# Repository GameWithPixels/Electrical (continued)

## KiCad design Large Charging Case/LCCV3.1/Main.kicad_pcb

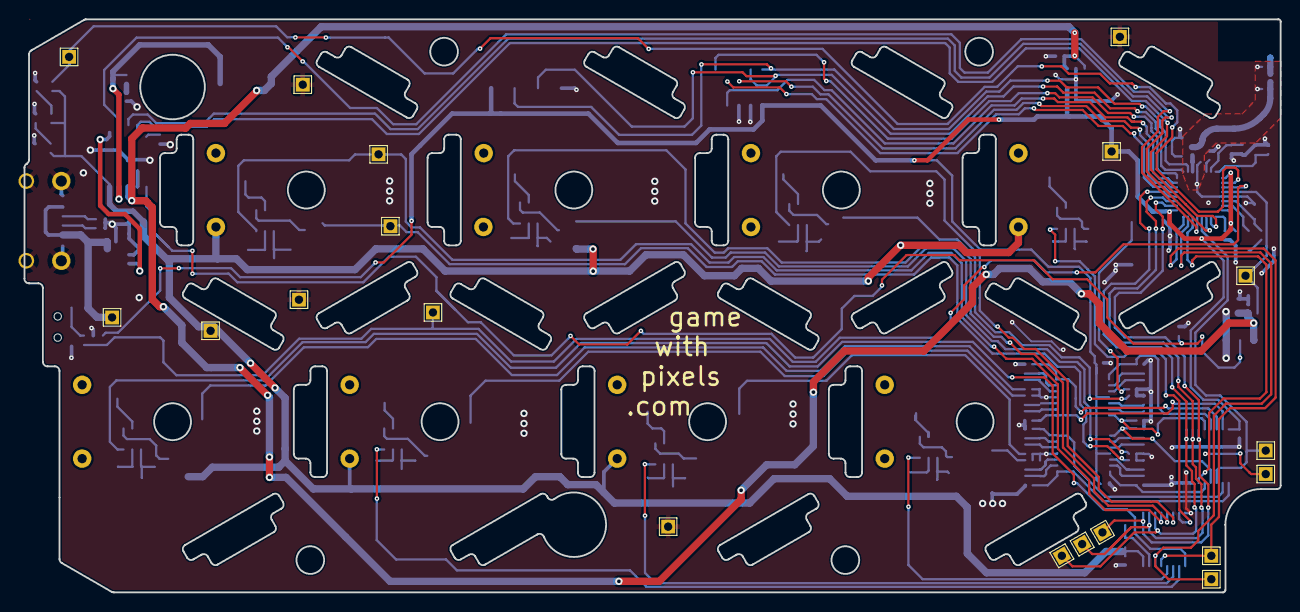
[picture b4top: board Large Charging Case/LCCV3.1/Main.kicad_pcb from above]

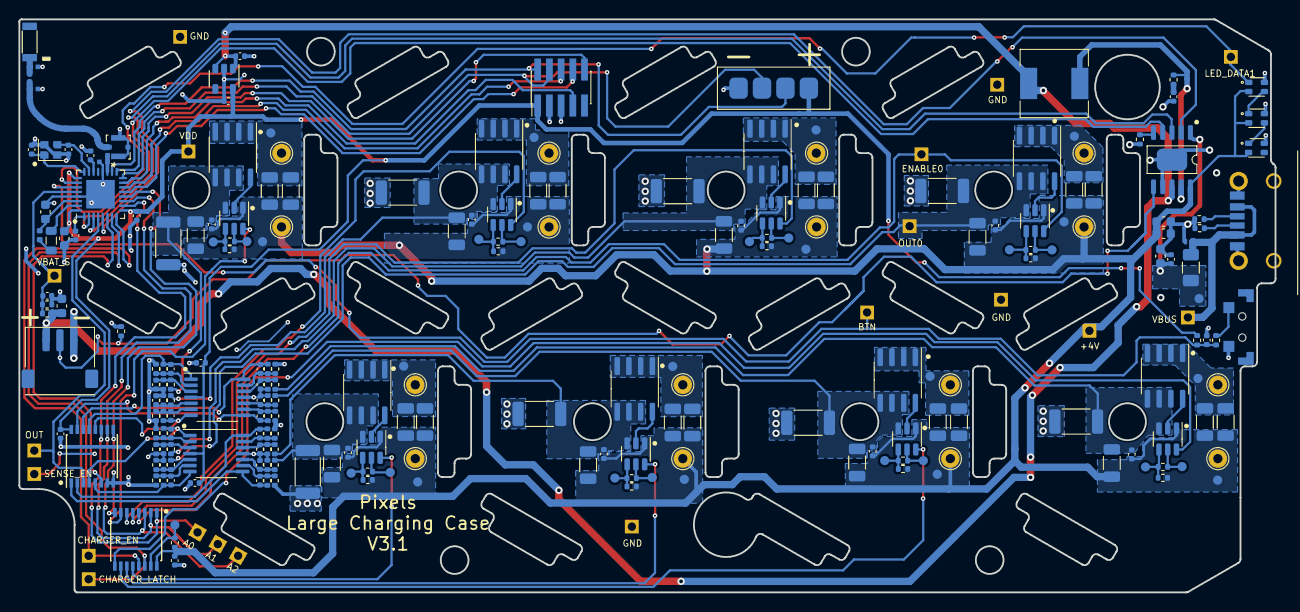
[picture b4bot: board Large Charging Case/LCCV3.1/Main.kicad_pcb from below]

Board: 2 copper layers, 136.2 x 62.1 mm, 256 parts (229 on the bottom side), 117 nets.

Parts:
+4V: +4V; TestPoint_1.5x1.5_Drill0.9mm
A0: A0; TestPoint_1.5x1.5_Drill0.9mm
A1: A1; TestPoint_1.5x1.5_Drill0.9mm
A2: A2; TestPoint_1.5x1.5_Drill0.9mm
AE1: Antenna_Chip; CHIP_ANT
BTN: BTN; TestPoint_1.5x1.5_Drill0.9mm
C1, C2: 4.7uF 6.3V 20%; C_0603_1608Metric
C3, C4, C10, C11, C15, C19, C23, C27, C31, C35, C39, C40, C41, C42, C43, C49, C50, C55, C59, C60, C61, C62, C63, C64, C65, C66, C67, C68, C69, C70, C71, C72: 0.1uF 10V 20%; C_0402_1005Metric
C5, C6: 8pF 10V 10%; C_0402_1005Metric
C7: 100pF NP0 10V 5%; C_0402_1005Metric
C8, C9: 0.8pF 10V 5% NP0; 0402_RF
C12, C16, C20, C24, C28, C32, C36, C56: 47uF 10V 20%; C_1206_3216Metric
C13, C17, C21, C25, C29, C33, C37, C57: 100nF 50V NP0; C_1206_3216Metric
C14, C18, C22, C26, C30, C34, C38, C58: 56nF 50V NP0; C_1206_3216Metric
C44, C45: 10uF 10V 20%; C_0603_1608Metric
C46: 3.3nF 10V 20%; C_0402_1005Metric
C47, C48: 22uF 10V 20%; C_0603_1608Metric
C52, C53: 10uF 10V 20%; C_0402_1005Metric
C54: 10nF 25V 10%; C_0402_1005Metric
C73: DNP; 0402_RF
CHARGER_EN: CHARGER_EN; TestPoint_1.5x1.5_Drill0.9mm
CHARGER_LATCH: CHARGER_LATCH; TestPoint_1.5x1.5_Drill0.9mm
D1, D2, D3: TX1812Z_2020
D5: D_TVS; DFN
ENABLE0: ENABLE0; TestPoint_1.5x1.5_Drill0.9mm
F1: 1500mA <150mR; Fuse_1206_3216Metric
GND: GND; TestPoint_1.5x1.5_Drill0.9mm
GND#2, GND#3, GND#4: GND; TestPoint_1.5x1.5_Drill0.9mm
J1: Conn_02x05_Odd_Even; PinHeader_2x05_P1.27mm_Vertical_SMD
J2, J5, J8, J11, J14, J17, J20, J25: Coil B; TestPoint_THTPad_D2.0mm_Drill1.0mm
J3, J6, J9, J12, J15, J18, J21, J26: TX_Coil; TX Coil
J4, J7, J10, J13, J16, J19, J22, J27: Coil A; TestPoint_THTPad_D2.0mm_Drill1.0mm
J23: USB_C_Receptacle_USB2.0; USB-C-SMD_10P-P1.00-L6.8-W8.9
J24: Conn_01x03; Battery_Socket_1.5mm_3PIN
J28: DNP; MFH3.RECE.20369.001E.01
L1: 10uH 100mA 10%; L_0805_2012Metric
L2: 15nH; L_0402_1005Metric
L3: 1.5nH 5%; 0402_RF
L4: 2.2uH 1.5A 10%; SPM6530
L6: 3.9nH 5%; 0402_RF
LED_DATA1: LED_DATA1; TestPoint_1.5x1.5_Drill0.9mm
OUT: OUT; TestPoint_1.5x1.5_Drill0.9mm
OUT0: OUT0; TestPoint_1.5x1.5_Drill0.9mm
P1: heard4; 4x2.54mm_SMD
R1: 10k 5%; R_0402_1005Metric
R2: 1k 1%; R_0402_1005Metric
R3, R5, R7, R9, R11, R13, R15, R37: 200k 1%; R_0402_1005Metric
R4, R6, R8, R10, R12, R14, R16, R38: 84.5k 1%; R_0402_1005Metric
R17: 82K 1%; R_0402_1005Metric
R18: 120k 1%; R_0402_1005Metric
R20: 100k 1%; R_0402_1005Metric
R21, R25, R28, R32, R39, R43, R44, R48, R49, R53, R54, R58, R59, R63, R64, R68: 100k 0.1%; R_0402_1005Metric
R22, R24, R29, R31, R40, R42, R45, R47, R50, R52, R55, R57, R60, R62, R65, R67: 2k 0.1%; R_0402_1005Metric
R23, R30, R41, R46, R51, R56, R61, R66: 100mR 0.5W 1%; R_2010_5025Metric
R26, R27: 5.1k 1%; R_0402_1005Metric
R34: 4.02M 1%; R_0402_1005Metric
R36: 10M 1%; R_0402_1005Metric
R69: 1R 5%; R_0402_1005Metric
SENSE_EN: SENSE_EN; TestPoint_1.5x1.5_Drill0.9mm
SW1: SW_Push; TSB002
U1: N52810_QFN32; QFN-32-1EP_5x5mm_P0.5mm_EP3.1x3.1mm
U2, U4, U6, U8, U10, U12, U14, U23: XKT001; SOT-23-6
U3, U5, U7, U9, U11, U13, U15, U24: XKT335; SOIC-8_3.9x4.9mm_P1.27mm
U16: ETA9882; ESSOP10
U17: 74HC4051PW; SSOP-16_4.4x5.2mm_P0.65mm
U18, U20: LM2902; TSSOP-14_4.4x5mm_P0.65mm
U19: 74HCT259; SSOP-16_4.4x5.2mm_P0.65mm
U22: ME6215; SOT-23-5
VBAT_S: VBAT_S; TestPoint_1.5x1.5_Drill0.9mm
VBUS: VBUS; TestPoint_1.5x1.5_Drill0.9mm
VDD: VDD; TestPoint_1.5x1.5_Drill0.9mm
W4, W5, W8, W9, W10, W13, W14, W15, W18, W19, W20, W23, W24, W25, W28, W29, W30, W33, W34, W35, W38, W71, W72, W75: R; TEST_PIN
W7, W12, W17, W22, W27, W32, W37, W74: D; TEST_PIN
W59: CHARGER_CLR; TEST_PIN
W62: 5V; TEST_PIN
Y1: 32MHz 40ppm; Crystal_SMD_2016-4Pin_2.0x1.6mm

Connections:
+4V: +4V.1, C11.1, C12.1, C13.2, C14.2, C15.1, C16.1, C17.2, C18.2, C19.1, C20.1, C21.2, C22.2, C23.1, C24.1, C25.2, C26.2, C27.1, C28.1, C29.2, C30.2, C31.1, C32.1, C33.2, C34.2, C35.1, C36.1, C37.2, C38.2, C42.1, C47.1, C48.1, C55.1, C56.1, C57.2, C58.2, D1.2 (VCC), D2.2 (VCC), D3.2 (VCC), J2.1, J5.1, J8.1, J11.1, J14.1, J17.1, J20.1, J25.1, R3.2, R5.2, R7.2, R9.2, R11.2, R13.2, R15.2, R20.1, R37.2, U2.1 (VDD), U4.1 (VDD), U6.1 (VDD), U8.1 (VDD), U10.1 (VDD), U12.1 (VDD), U14.1 (VDD), U16.10 (VOUT), U19.16 (VCC), U23.1 (VDD), W4.1, W9.1, W14.1, W19.1, W24.1, W29.1, W34.1, W71.1
+5V: C43.1, C44.1, F1.2, U16.1 (VIN), W62.1
+BATT: C45.1, C53.1, J24.3, L4.2, R34.1, U16.8 (BAT), U22.1 (VIN), U22.3 (CE)
/ANTENNA: AE1.1 (FEED), C73.1, L3.2
/ANT_50: C8.1, J28.4 (RF), L3.1, L6.2
/ANT_NRF: C9.1, L6.1, U1.19 (ANT)
/Multiplexed Chargers/CHARGER_ENL_D: CHARGER_EN.1, U1.8 (P0.10), U19.13 (D)
/Multiplexed Chargers/CHARGER_SELECT_A0: A0.1, U1.10 (P0.12), U17.11 (A), U19.1 (A0)
/Multiplexed Chargers/CHARGER_SELECT_A1: A1.1, U1.11 (P0.14), U17.10 (B), U19.2 (A1)
/Multiplexed Chargers/CHARGER_SELECT_A2: A2.1, U1.12 (P0.15), U17.9 (C), U19.3 (A2)
/Multiplexed Chargers/Charger 1/CHARGER_GND: C23.2, C24.2, OUT0.1, R23.2, R24.1, U8.3 (GND), U9.5 (S), U9.6 (S), U9.7 (S)
/Multiplexed Chargers/Charger 2/CHARGER_GND: C11.2, C12.2, R30.2, R31.1, U2.3 (GND), U3.5 (S), U3.6 (S), U3.7 (S)
/Multiplexed Chargers/Charger 3/CHARGER_GND: C15.2, C16.2, R56.2, R57.1, U4.3 (GND), U5.5 (S), U5.6 (S), U5.7 (S)
/Multiplexed Chargers/Charger 4/CHARGER_GND: C19.2, C20.2, R51.2, R52.1, U6.3 (GND), U7.5 (S), U7.6 (S), U7.7 (S)
/Multiplexed Chargers/Charger 5/CHARGER_GND: C55.2, C56.2, R41.2, R42.1, U23.3 (GND), U24.5 (S), U24.6 (S), U24.7 (S)
/Multiplexed Chargers/Charger 6/CHARGER_GND: C27.2, C28.2, R46.2, R47.1, U10.3 (GND), U11.5 (S), U11.6 (S), U11.7 (S)
/Multiplexed Chargers/Charger 7/CHARGER_GND: C31.2, C32.2, R61.2, R62.1, U12.3 (GND), U13.5 (S), U13.6 (S), U13.7 (S)
/Multiplexed Chargers/Charger 8/CHARGER_GND: C35.2, C36.2, R66.2, R67.1, U14.3 (GND), U15.5 (S), U15.6 (S), U15.7 (S)
/Multiplexed Chargers/ENABLE0: ENABLE0.1, U8.6 (N/F), U19.4 (Q0)
/Multiplexed Chargers/ENABLE1: U2.6 (N/F), U19.5 (Q1)
/Multiplexed Chargers/ENABLE2: U4.6 (N/F), U19.6 (Q2)
/Multiplexed Chargers/ENABLE3: U6.6 (N/F), U19.7 (Q3)
/Multiplexed Chargers/ENABLE4: U14.6 (N/F), U19.9 (Q4)
/Multiplexed Chargers/ENABLE5: U12.6 (N/F), U19.10 (Q5)
/Multiplexed Chargers/ENABLE6: U10.6 (N/F), U19.11 (Q6)
/Multiplexed Chargers/ENABLE7: U19.12 (Q7), U23.6 (N/F)
/Multiplexed Chargers/SENSE0: C49.2, R21.1, U17.5 (X5), U18.7
/Multiplexed Chargers/SENSE1: C59.2, R28.1, U17.4 (X7), U18.1
/Multiplexed Chargers/SENSE2: C67.2, R54.1, U17.12 (X3), U20.7
/Multiplexed Chargers/SENSE3: C65.2, R49.1, U17.13 (X0), U20.1
/Multiplexed Chargers/SENSE4: C61.2, R39.1, U17.1 (X4), U18.8
/Multiplexed Chargers/SENSE5: C63.2, R44.1, U17.2 (X6), U18.14
/Multiplexed Chargers/SENSE6: C69.2, R59.1, U17.15 (X2), U20.8
/Multiplexed Chargers/SENSE7: C71.2, R64.1, U17.14 (X1), U20.14
/Multiplexed Chargers/SENSE_EN: SENSE_EN.1, U1.6 (P0.06), U17.6 (ENABLE)
/Multiplexed Chargers/SENSE_OUT: OUT.1, U1.4 (P0.04/AIN2), U17.3 (X)
/Multiplexed Chargers/~CHARGER_ENL_EN: CHARGER_LATCH.1, U1.7 (P0.09), U19.14 (E)
/Power/4V_EN: U1.3 (P0.01/XL2), U16.3 (ENBST)
/Power/BAT_STAT: U1.5 (P0.05/AIN3), U16.2 (STAT)
/Power/CHARGE: U1.2 (P0.00/XL1), U16.4 (ENCHRG)
/Power/VBAT_SENSE: C54.1, R34.2, R36.1, U1.28 (P0.30/AIN6), VBAT_S.1
GND: C1.2, C2.2, C3.2, C4.2, C5.1, C6.1, C7.2, C8.2, C9.2, C10.2, C39.2, C40.2, C41.2, C42.2, C43.2, C44.2, C45.2, C46.2, C47.2, C48.2, C50.2, C52.2, C53.2, C54.2, C60.2, C62.2, C64.2, C66.2, C68.2, C70.2, C72.2, C73.2, D1.4 (GND), D2.4 (GND), D3.4 (GND), D5.1 (A1), GND.1, GND#2.1, GND#3.1, GND#4.1, J1.3, J1.5, J23.A12 (GND), J23.B12 (GND), J23.S1 (SHIELD), J24.1, J28.1, J28.2, J28.3, P1.4, R17.1, R18.2, R22.1, R23.1, R25.1, R26.1, R27.1, R29.1, R30.1, R32.1, R36.2, R40.1, R41.1, R43.1, R45.1, R46.1, R48.1, R50.1, R51.1, R53.1, R55.1, R56.1, R58.1, R60.1, R61.1, R63.1, R65.1, R66.1, R68.1, SW1.2, U1.20 (VSS), U1.29 (VSS), U1.33 (VSS), U16.7 (VTERM), U16.11 (GND), U17.7 (V-), U17.8 (GND), U18.11 (V-), U19.8 (GND), U20.11 (V-), U22.2 (VSS), Y1.2, Y1.4
unnamed: C1.1, L2.2, U1.30 (DEC4)
unnamed: BTN.1, C3.1, R1.1, R2.2, U1.27 (P0.28/AIN4)
unnamed: C4.1, U1.1 (DEC1)
unnamed: C5.2, U1.24 (XC2), Y1.1
unnamed: C6.2, U1.23 (XC1), Y1.3
unnamed: C7.1, U1.22 (DEC3)
unnamed: C13.1, C14.1, J4.1, U3.1 (D), U3.2 (D), U3.3 (D), U3.4 (D), W7.1
unnamed: C17.1, C18.1, J7.1, U5.1 (D), U5.2 (D), U5.3 (D), U5.4 (D), W12.1
unnamed: C21.1, C22.1, J10.1, U7.1 (D), U7.2 (D), U7.3 (D), U7.4 (D), W17.1
unnamed: C25.1, C26.1, J13.1, U9.1 (D), U9.2 (D), U9.3 (D), U9.4 (D), W22.1
unnamed: C29.1, C30.1, J16.1, U11.1 (D), U11.2 (D), U11.3 (D), U11.4 (D), W27.1
unnamed: C33.1, C34.1, J19.1, U13.1 (D), U13.2 (D), U13.3 (D), U13.4 (D), W32.1
unnamed: C37.1, C38.1, J22.1, U15.1 (D), U15.2 (D), U15.3 (D), U15.4 (D), W37.1
unnamed: C46.1, R69.1
unnamed: C49.1, R21.2, R22.2, U18.6 (-)
unnamed: C50.1, R24.2, R25.2, U18.5 (+)
unnamed: C57.1, C58.1, J27.1, U24.1 (D), U24.2 (D), U24.3 (D), U24.4 (D), W74.1
unnamed: C59.1, R28.2, R29.2, U18.2 (-)
unnamed: C60.1, R31.2, R32.2, U18.3 (+)
unnamed: C61.1, R39.2, R40.2, U18.9 (-)
unnamed: C62.1, R42.2, R43.2, U18.10 (+)
unnamed: C63.1, R44.2, R45.2, U18.13 (-)
unnamed: C64.1, R47.2, R48.2, U18.12 (+)
unnamed: C65.1, R49.2, R50.2, U20.2 (-)
unnamed: C66.1, R52.2, R53.2, U20.3 (+)
unnamed: C67.1, R54.2, R55.2, U20.6 (-)
unnamed: C68.1, R57.2, R58.2, U20.5 (+)
unnamed: C69.1, R59.2, R60.2, U20.9 (-)
unnamed: C70.1, R62.2, R63.2, U20.10 (+)
unnamed: C71.1, R64.2, R65.2, U20.13 (-)
unnamed: C72.1, R67.2, R68.2, U20.12 (+)
unnamed: D1.1 (DIN), D2.3 (DOUT)
unnamed: D2.1 (DIN), D3.3 (DOUT)
unnamed: D3.1 (DIN), LED_DATA1.1, U1.26 (P0.25)
unnamed: J23.A5 (CC1), R27.2
unnamed: J23.B5 (CC2), R26.2
unnamed: J24.2, R17.2, U16.6 (NTC)
unnamed: L1.1, U1.31 (DCC)
unnamed: L1.2, L2.1
unnamed: L4.1, R69.2, U16.9 (SW)
unnamed: R2.1, SW1.1
unnamed: R3.1, R4.1, U2.4 (R), W8.1
unnamed: R4.2, U2.5 (R), W5.1
unnamed: R5.1, R6.1, U4.4 (R), W13.1
unnamed: R6.2, U4.5 (R), W10.1
unnamed: R7.1, R8.1, U6.4 (R), W18.1
unnamed: R8.2, U6.5 (R), W15.1
unnamed: R9.1, R10.1, U8.4 (R), W23.1
unnamed: R10.2, U8.5 (R), W20.1
unnamed: R11.1, R12.1, U10.4 (R), W28.1
unnamed: R12.2, U10.5 (R), W25.1
unnamed: R13.1, R14.1, U12.4 (R), W33.1
unnamed: R14.2, U12.5 (R), W30.1
unnamed: R15.1, R16.1, U14.4 (R), W38.1
unnamed: R16.2, U14.5 (R), W35.1
unnamed: R18.1, U16.5 (ISET)
unnamed: R20.2, U19.15 (Clr), W59.1
unnamed: R37.1, R38.1, U23.4 (R), W75.1
unnamed: R38.2, U23.5 (R), W72.1
unnamed: U2.2 (OUT), U3.8 (G)
unnamed: U4.2 (OUT), U5.8 (G)
unnamed: U6.2 (OUT), U7.8 (G)
unnamed: U8.2 (OUT), U9.8 (G)
unnamed: U10.2 (OUT), U11.8 (G)
unnamed: U12.2 (OUT), U13.8 (G)
unnamed: U14.2 (OUT), U15.8 (G)
unnamed: U23.2 (OUT), U24.8 (G)
RESET: J1.10, U1.16 (P0.16)
RXI: J1.7, U1.15 (P0.20/TCLK)
SWDCLK: J1.4, P1.3, U1.17 (SWDCLK)
SWDIO: J1.2, P1.2, U1.18 (SWDIO)
SWO: J1.6, U1.14 (P0.18/TDATA0)
TXO: J1.8, U1.13 (P0.16/TDATA1)
VBUS: D5.2 (A2), F1.1, J23.A9 (VBUS), J23.B9 (VBUS), VBUS.1
VDD: C2.1, C10.1, C39.1, C40.1, C41.1, C52.1, J1.1, P1.1, R1.2, U1.9 (VDD), U1.25 (VDD), U1.32 (VDD), U17.16 (V+), U18.4 (V+), U20.4 (V+), U22.5 (VOUT), VDD.1

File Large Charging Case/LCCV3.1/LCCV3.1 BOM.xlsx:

Source: | C:\Projects\Pixels-dice\Electrical\Large Charging Case\LCCV3.1\Main.kicad_sch
Date: | 44909.681793981479
Item | Qty | Reference(s) | Value | Footprint | Generic OK | Manufacturer | Manufacturer Part Number
1 | 1 | AE1 | Antenna_Chip | Pixels-dice:CHIP_ANT | NO | Microgate | MGMA3216H2450-A02
2 | 2 | C1, C2 | 4.7uF 6.3V 20% | Capacitor_SMD:C_0603_1608Metric | YES | Murata | GRM188R61A475KE15D
3 | 32 | C3, C4, C10, C11, C15, C19, C23, C27, C31, C35, C39, C40, C41, C42, C43, C49, C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 | 0.1uF 10V 20% | Capacitor_SMD:C_0402_1005Metric | YES | Murata | GRM155R61H104KE19D
4 | 2 | C5, C6 | 8pF 10V 10% | Capacitor_SMD:C_0402_1005Metric | YES | Murata | GRT1555C2A8R0DA02
5 | 1 | C7 | 100pF NP0 10V 5% | Capacitor_SMD:C_0402_1005Metric | YES | Murata | GCM1555C1H101JA16J
6 | 2 | C8, C9 | 0.8pF 10V 5% NP0 | Pixels-dice:0402_RF | YES | Murata | GJM1555C1HR80BB01
7 | 8 | C12, C16, C20, C24, C28, C32, C36, C56 | 47uF 10V 20% | Capacitor_SMD:C_1206_3216Metric | YES | Murata | GRM31CR61A476ME15L
8 | 8 | C13, C17, C21, C25, C29, C33, C37, C57 | 100nF 50V NP0 | Capacitor_SMD:C_1206_3216Metric | NO | Murata | GRM31C5C1H104JA01L
9 | 8 | C14, C18, C22, C26, C30, C34, C38, C58 | 56nF 50V NP0 | Capacitor_SMD:C_1206_3216Metric | NO | Murata | GRM31M5C1H563JA01L
10 | 2 | C44, C45 | 10uF 10V 20% | Capacitor_SMD:C_0603_1608Metric | YES | Murata | GRM188R61A106ME69D
11 | 1 | C46 | 3.3nF 10V 20% | Capacitor_SMD:C_0402_1005Metric | YES | Murata | GCM1555C1H220JA16J
12 | 2 | C47, C48 | 22uF 10V 20% | Capacitor_SMD:C_0603_1608Metric | YES | Murata | GRM188R61A226ME15D
13 | 2 | C52, C53 | 10uF 10V 20% | Capacitor_SMD:C_0402_1005Metric | YES | Murata | GRM155R61A106ME11D
14 | 1 | C54 | 10nF 25V 10% | Capacitor_SMD:C_0402_1005Metric | YES | Murata | GRM155R71H103KA88
15 | 3 | D1, D2, D3 | TX1812Z_2020 | Pixels-dice:TX1812Z_2020 | NO | TCWIN | TC2020RGB-3CJH-TX1812Z5
16 | 1 | D5 | D_TVS | Pixels-dice:DFN |  | Murata | LXES1UTAA1-157
17 | 1 | F1 | 1500mA <150mR | Fuse:Fuse_1206_3216Metric | YES | Shenzhen JDT Fuse | ASMD1206-150
18 | 1 | J1 | Conn_02x05_Odd_Even | Connector_PinHeader_1.27mm:PinHeader_2x05_P1.27mm_Vertical_SMD | YES | XKB Connectivity | X1270WVS-2x05B-6TV01
22 | 1 | J23 | USB_C_Receptacle_USB2.0 | Pixels-dice:USB-C-SMD_10P-P1.00-L6.8-W8.9 | NO | Korean Hroparts Elec | TYPE-C-31-M-17
23 | 1 | J24 | Conn_01x03 | Pixels-dice:Battery_Socket_1.5mm_3PIN |  | ZH CONNECTOR | S3B-ZR-SM4A-TF
24 | 1 | L1 | 10uH 100mA 10% | Inductor_SMD:L_0805_2012Metric | YES | Murata | LQM21FN100M80L
25 | 1 | L2 | 15nH | Inductor_SMD:L_0402_1005Metric | YES | Murata | LQG15HS15NJ02D
26 | 1 | L3 | 1.5nH 5% | Pixels-dice:0402_RF | YES | Murata | LQG15WZ1N5B02D
27 | 1 | L4 | 2.2uH 1.5A 10% | Pixels-dice:SPM6530 | YES | TDK | SPM6530T-2R2M
28 | 1 | L6 | 3.9nH 5% | Pixels-dice:0402_RF | YES | Murata | LQG15HS3N9B02D
29 | 1 | P1 | heard4 | Pixels-dice:4x2.54mm_SMD
30 | 1 | R1 | 10k 5% | Resistor_SMD:R_0402_1005Metric | YES | UNI-ROYAL(Uniroyal Elec) | 0402WGF1002TCE
31 | 1 | R2 | 1k 1% | Resistor_SMD:R_0402_1005Metric | YES | UNI-ROYAL(Uniroyal Elec) | 0402WGF1001TCE
32 | 8 | R3, R5, R7, R9, R11, R13, R15, R37 | 200k 1% | Resistor_SMD:R_0402_1005Metric | YES | UNI-ROYAL(Uniroyal Elec) | 0402WGF2003TCE
33 | 8 | R4, R6, R8, R10, R12, R14, R16, R38 | 84.5k 1% | Resistor_SMD:R_0402_1005Metric | YES | UNI-ROYAL(Uniroyal Elec) | 0402WGF8452TCE
34 | 1 | R17 | 82K 1% | Resistor_SMD:R_0402_1005Metric | YES | UNI-ROYAL(Uniroyal Elec) | 0402WGF8202TCE
35 | 1 | R18 | 120k 1% | Resistor_SMD:R_0402_1005Metric | YES | UNI-ROYAL(Uniroyal Elec) | 0402WGF1203TCE
36 | 1 | R20 | 100k 1% | Resistor_SMD:R_0402_1005Metric | YES | UNI-ROYAL(Uniroyal Elec) | 0402WGF1003TCE
37 | 16 | R21, R25, R28, R32, R39, R43, R44, R48, R49, R53, R54, R58, R59, R63, R64, R68 | 100k 0.1% | Resistor_SMD:R_0402_1005Metric | NO | UNI-ROYAL(Uniroyal Elec) | TC0225B1003TCC
38 | 16 | R22, R24, R29, R31, R40, R42, R45, R47, R50, R52, R55, R57, R60, R62, R65, R67 | 2k 0.1% | Resistor_SMD:R_0402_1005Metric | YES | YAGEO | RT0402BRD072KL
39 | 8 | R23, R30, R41, R46, R51, R56, R61, R66 | 100mR 0.5W 1% | Resistor_SMD:R_2010_5025Metric | NO | YAGEO | RL2010FK-070R1L
40 | 2 | R26, R27 | 5.1k 1% | Resistor_SMD:R_0402_1005Metric | YES | UNI-ROYAL(Uniroyal Elec) | 0402WGF5101TCE
41 | 1 | R34 | 4.02M 1% | Resistor_SMD:R_0402_1005Metric | YES | UNI-ROYAL(Uniroyal Elec) | 0402WGF4024TCE
42 | 1 | R36 | 10M 1% | Resistor_SMD:R_0402_1005Metric | YES | UNI-ROYAL(Uniroyal Elec) | 0402WGF1005TCE
43 | 1 | R69 | 1R 5% | Resistor_SMD:R_0402_1005Metric | YES | UNI-ROYAL(Uniroyal Elec) | 0402WGJ010JTCE
44 | 1 | SW1 | SW_Push | Pixels-dice:TSB002 | NO | BZCN | TSB001A3526A02
45 | 1 | U1 | N52810_QFN32 | Package_DFN_QFN:QFN-32-1EP_5x5mm_P0.5mm_EP3.1x3.1mm | NO | Nordic Semiconductor | NRF52810-QCAA-R
46 | 8 | U2, U4, U6, U8, U10, U12, U14, U23 | XKT001 | Package_TO_SOT_SMD:SOT-23-6 | NO | XKT | XKT-001
47 | 8 | U3, U5, U7, U9, U11, U13, U15, U24 | XKT335 | Pixels-dice:SOIC-8_3.9x4.9mm_P1.27mm | NO | XKT | XKT-335
48 | 1 | U16 | ETA9882 | Pixels-dice:ESSOP10 |  | ETA Semiconductor Limited | ETA9882E10
49 | 1 | U17 | 74HC4051PW | Package_SO:SSOP-16_4.4x5.2mm_P0.65mm | NO | Nexperia | 74HC4051PW,118
50 | 2 | U18, U20 | LM2902 | Package_SO:TSSOP-14_4.4x5mm_P0.65mm |  | Texas Instrument | LM2902PWR
51 | 1 | U19 | 74HCT259 | Package_SO:SSOP-16_4.4x5.2mm_P0.65mm | NO | Nexperia | 74HCT259D
52 | 1 | U22 | ME6215 | Pixels-dice:SOT-23-5 | NO | MICRONE(Nanjing Micro One Elec) | ME6215C30M5G
73 | 1 | Y1 | 32MHz 40ppm | Pixels-dice:Crystal_SMD_2016-4Pin_2.0x1.6mm | YES | Murata | XRCGB32M000F2P00R0
